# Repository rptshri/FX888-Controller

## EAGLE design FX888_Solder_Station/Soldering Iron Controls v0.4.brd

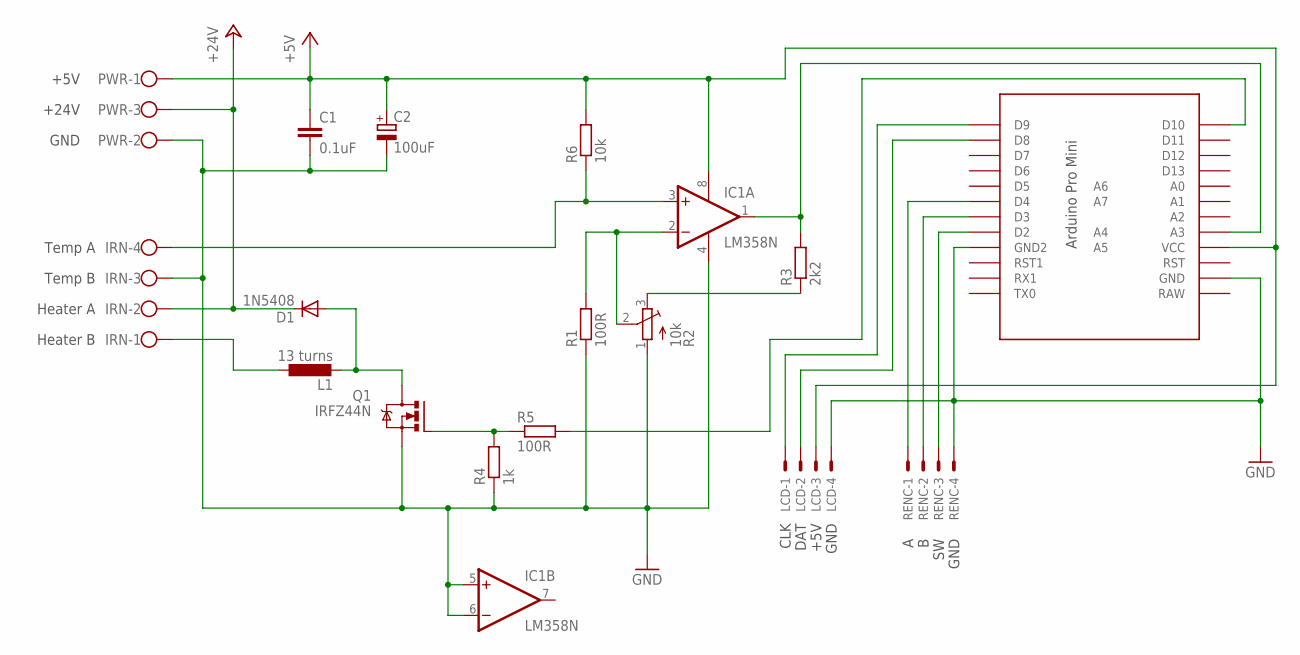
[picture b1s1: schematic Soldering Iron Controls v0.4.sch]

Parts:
C1: 0.1uF; C025-024X044
C2: 100uF; E5-6
D1: 1N5408; DO27-15
IC1: LM358N; DIL08
IRN: W237-4
L1: 13 turns; TJ3-U1
LCD: 22-05-7048-04; 7395-04
PWR: W237-103
Q1: IRFZ44N; TO220BV
R1, R5: 100R; 0207/7@1
R2: 10k; RM-065
R3: 2k2; 0207/7@1
R4: 1k; 0207/7@1
R6: 10k; 0207/7@1
RENC: 22-05-7048-04; 7395-04
U$1: PRO-MINI-2X

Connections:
+5V: C1.1, C2.+, IC1.8 (V+), LCD.3, PWR.1, R6.2, U$1.VCC
+24V: D1.C, IRN.2, PWR.3
GND: C1.2, C2.-, IC1.4 (V-), IC1.5 (+IN), IC1.6 (-IN), IRN.3, LCD.4, PWR.2, Q1.S, R1.1, R2.1 (A), R4.1, RENC.4, U$1.GND, U$1.GND1 (GND2)
unnamed: R2.3 (E), R3.1
unnamed: IRN.1, L1.1
unnamed: D1.A, L1.2, Q1.D
unnamed: IC1.2 (-IN), R1.2, R2.2 (S)
unnamed: R5.2, U$1.D10
unnamed: IC1.1 (OUT), R3.2, U$1.A3
unnamed: RENC.3, U$1.D2
unnamed: RENC.2, U$1.D3
unnamed: RENC.1, U$1.D4
unnamed: IC1.3 (+IN), IRN.4, R6.1
unnamed: Q1.G, R4.2, R5.1
unnamed: LCD.2, U$1.D8
unnamed: LCD.1, U$1.D9

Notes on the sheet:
Heater B
Heater A
Temp B
GND
DAT
CLK
+5V
Temp A
+24V

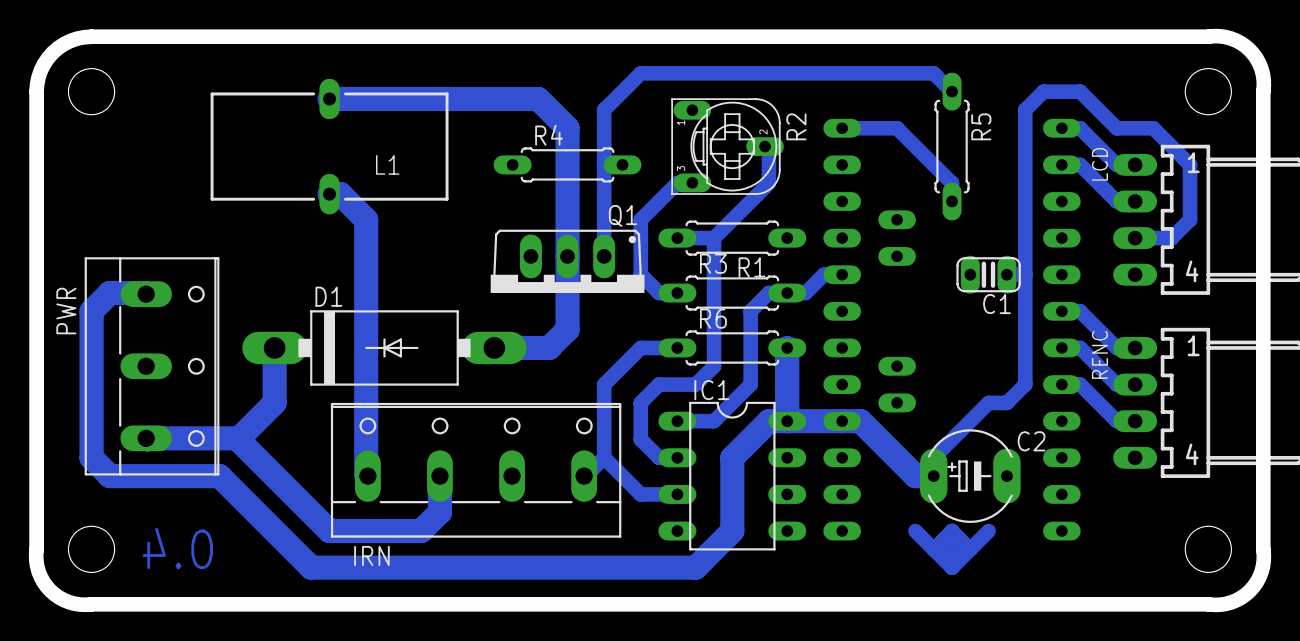
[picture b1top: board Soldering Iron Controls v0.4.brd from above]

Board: 2 copper layers, 85.2 x 39.4 mm, 17 parts (0 on the bottom side), 16 nets.

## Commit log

2017-12-01 AddedPCB files
2017-12-02 Added PCB files
    These are the original PCB files by the author.
    I thought these should be in the repositary, so I added it
2020-05-25 [ImgBot] Optimize images
    *Total -- 748.83kb -> 629.52kb (15.93%)
    /media/photo/SS_Tuning_Separated.png -- 52.83kb -> 30.96kb (41.39%)
    /media/photo/SS_PID.png -- 22.19kb -> 13.40kb (39.59%)
    /media/photo/SS_Tuning_6.png -- 40.63kb -> 25.28kb (37.78%)
    /media/photo/SS_PID_Algorithm.png -- 18.08kb -> 11.84kb (34.52%)
    /media/photo/SS_Display_Design.jpg -- 57.06kb -> 46.78kb (18.03%)
